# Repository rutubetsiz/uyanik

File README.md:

# UYANIK

[Türkçe](README.tr.md)

A device for turning a remote computer on and off. As long as you have internet access, it doesn’t matter where in the world you are.
## Why did I build this?

It started as a summer project. I had turned a spare computer into a server, but I didn’t want to leave it running all the time. University was about to start, and I needed a way to turn it on and off remotely. Shutting down a remote machine is easy, turning it on is not. Wake-on-LAN isn’t enough, and if you’re behind CGNAT on top of that... The answer to all of it was a device that stays on at home, so I built one. Wherever I am, UYANIK lets me open a web panel and turn my server on and off as if I were at home pressing the button on the case.

## How it works

The device connects to the motherboard’s front panel header (JFP1). When a command comes in, the optocoupler switches and the motherboard sees it as a button press. By reading the power LED line on the same header, it also knows whether the computer is on or off.

Since the device takes up the header, the case’s front panel is left out; there’s nowhere to plug in the case’s power button, reset button and LED. That’s why the device has its own power and reset buttons, plus an LED that shows whether the computer is on. So you don’t lose the case button, it just moves onto the device.

Commands go through Firebase Realtime Database. When you send a command from the panel, it’s written to a field in the database; the device polls that field and runs the command when it sees it. Status comes back the same way in the other direction.

The reason for Firebase is that the device and the phone are on different networks, usually behind CGNAT. A direct connection isn’t possible, so a meeting point is needed. No port forwarding, DDNS or static IP required.

Besides the remote panel there’s also a local panel. It lives in the device’s own flash and works without internet. If you’re on the same network, you can connect to the device directly and send commands. When the device can’t connect to any network, it opens its own hotspot and the same panel shows up as the setup screen.

The device has to keep running while the computer is off, after all it’s the thing that turns the machine on. I power it from the motherboard’s USB header, JUSB2. While the computer is off, the power on that header actually comes from the power supply’s standby line, which stays live as long as the plug is in. The motherboard doesn’t feed it to the header by default, so two BIOS settings need to be changed. Details are below under Power.

## Hardware

### Pins

GPIO25 drives the power button’s optocoupler, GPIO26 the reset button’s. GPIO27 reads the signal coming from the power LED’s optocoupler.

GPIO4 is reserved for factory reset. There’s no button for it on the board; to reset, short this pin to GND and hold it for five seconds without interruption.

GPIO32 was added in version 2. It drives an LED output that shows the computer is on.

### Parts

- ESP32-WROOM-32D
- 3x PC817 DIP-4 optocoupler
- 3x 470 ohm resistor
- 2x 3.5x6mm tact switch
- LED
- 3-pin slide on/off switch

To connect to JFP1, female front panel cables are enough if you can find them. Otherwise you can modify female-to-female jumper wires.

### Why an optocoupler?

I tried, as much as I could, to make this work on motherboards from different manufacturers, not just one. An optocoupler wasn’t strictly necessary; the buttons could have been driven with transistors and the power LED read directly through resistors. I chose the optocoupler because it doesn’t require making assumptions about the motherboard’s internal circuitry. The buttons’ pull-up voltage or which side the LED is driven from can vary from board to board, while an optocoupler works the same way on all of them. Since the cost difference is tiny, I went with the solution that isn’t affected by differences between boards.

### Power

The device needs to stay up while the computer is off. There are a few ways to do this.

One is from the motherboard, through the JUSB headers. This is how I did it. But there’s a catch: with default settings, the motherboard doesn’t supply standby power to the USB headers while it’s off. You need to change BIOS settings. The first is EuP 2013 or ErP Ready (the name depends on your board); on MSI it’s under Advanced, in the Power Management Setup menu. Set it to Disabled. The second is Resume By USB Device, also under Advanced but in the Wake Up Event Setup menu. Set it to Enabled. Measure between the header’s VCC and GND pins, you should see around 5 V. If you don’t, try the other header; some motherboards only supply standby power to certain ports. The downside: when the power goes out or the motherboard loses power, the device can’t get power until the computer is started by hand.

Another is directly from the power supply, pin 9 of the 24-pin connector. The purple wire. It’s completely independent of the BIOS because you’re taking power before the motherboard distributes it; no setting can turn it off. In return, you need a breakout board or a tap connector in between. If you don’t want to mess with the BIOS, or your motherboard never gives standby power to the headers, this way will definitely work.

A third option is to power the device directly from a battery or an adapter. The current design isn’t set up for that, so it would need modification.

### PCB

hardware/ contains the KiCad project and PDF exports.

I made the PCB myself, so I designed it to suit home etching. You can make it yourself, or open the KiCad project, change it to your liking and send it off to be manufactured. None of this is required, the circuit works on a breadboard too.

### Case

case/ contains the model.

You can 3D print it. All the parts are in one file, so you may need to separate them.

## Setup

### 1. Firmware

It builds with the Arduino IDE. The folder name has to match the .ino file, so open the software/UYANIK/ folder as it is.

If you edit panel.html, you need to regenerate the copy that gets embedded in the device:

```bash
python build_html.py
```

To check whether the two match:

```bash
python build_html.py --kontrol
```

### 2. First boot

On first boot the device prints three values to the serial port: the hotspot network name, the panel password and the OTA password.

```
SSID : UYANIK-XXXX
Password : ...
OTA : ...
```

Save these somewhere. They don’t change on factory reset. If you change the panel password later, the value here stops working, but a factory reset brings it back.

### 3. Wi-Fi

If no network is saved, the device opens its own hotspot. Once your phone is connected, go to uyanik.local to open the panel; if that doesn’t work, use 192.168.4.1.

After it joins a network, you can reach the device at uyanik.local or at the local IP shown in the panel. The hotspot stays up for another 25 seconds so you can see the new address.

### 4. Firebase

Everyone sets up their own Firebase project.

Create a new project in the Firebase console and add a Realtime Database to it. In the Authentication section, enable the Email/Password provider and create an account for the device.

Finally, lock the database rules to that account’s UID:

```json
{
  "rules": {
      ".read":  "auth != null && auth.uid === 'UID'",
      ".write": "auth != null && auth.uid === 'UID'"
  }
}
```

Once that’s done, enter the following in the Settings tab of the device’s panel: the Realtime Database URL, the Web API Key, the email and password of the account you created, and a device name.

### 5. Remote panel

software/web/public/index.html is a single static page and can be used in two ways.

To deploy it to Firebase Hosting, from the software/web/ folder:

```bash
firebase use --add
```

```bash
firebase deploy --only hosting
```

Since it’s a static file, you can also host it on your own server.

You can also open it directly via file://.

When the panel first opens, it asks for the database URL, the Web API Key and the device name. These are only stored in the browser and are never sent anywhere.

## Factory reset

Short GPIO 4 to GND and hold it for five seconds without interruption. A single break resets the counter.

A reset erases the Wi-Fi network and its password, the Firebase settings, the device and hotspot names, and the panel password if you changed it. It does not touch the panel and OTA passwords generated on first boot.

## Read more

- [Troubleshooting](docs/TROUBLESHOOTING.md)
- [Firmware structure](docs/FIRMWARE.md)

## License

GPL-3.0. See [LICENSE](LICENSE) for details.

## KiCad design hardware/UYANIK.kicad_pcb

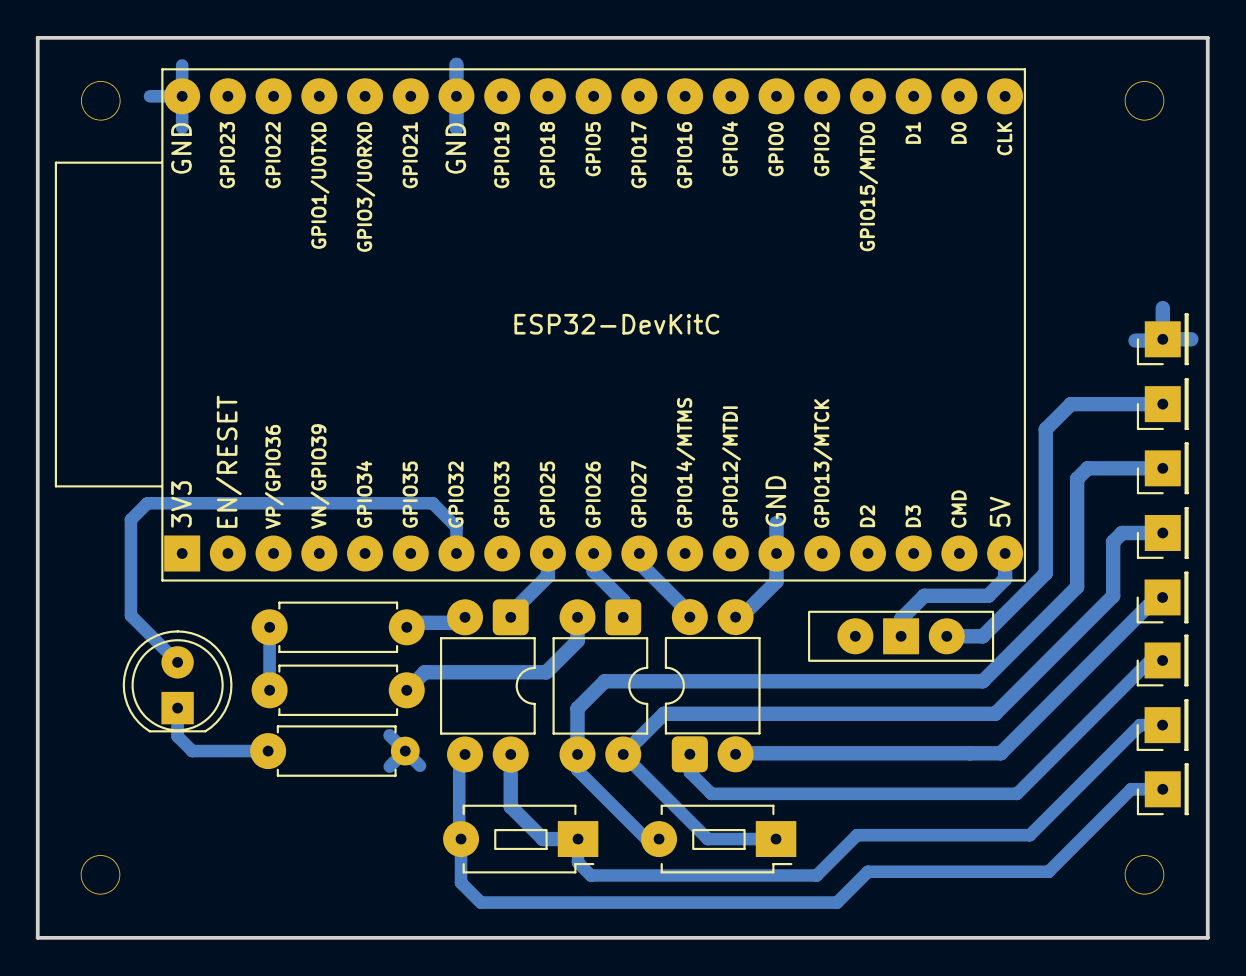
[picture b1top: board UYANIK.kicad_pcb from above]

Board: 2 copper layers, 65.0 x 50.0 mm, 19 parts (0 on the bottom side), 16 nets.

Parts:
D1: POWER LED; LED_D5.0mm
J1: POWER SW+; PinHeader_1x01_P2.54mm_Vertical
J2: POWER SW-; PinHeader_1x01_P2.54mm_Vertical
J3: RESET SW+; PinHeader_1x01_P2.54mm_Vertical
J4: RESET SW-; PinHeader_1x01_P2.54mm_Vertical
J5: POWER LED+; PinHeader_1x01_P2.54mm_Vertical
J6: POWER LED-; PinHeader_1x01_P2.54mm_Vertical
J13: VSS; PinHeader_1x01_P2.54mm_Vertical
J14: VCC; PinHeader_1x01_P2.54mm_Vertical
R1, R2, R3: 470; R_Axial_DIN0207_L6.3mm_D2.5mm_P7.62mm_Horizontal
SW1: SW_RESET; SW_PUSH_1P1T_6x3.5mm_H4.3_APEM_MJTP1243
SW2: SW_POWER; SW_PUSH_1P1T_6x3.5mm_H4.3_APEM_MJTP1243
SW3: ON / OFF; SW_Slide-03_Wuerth-WS-SLTV_10x2.5x6.4_P2.54mm
U2: RST OPT; DIP-4_W7.62mm
U3: ESP32-DevKitC
U4: PWR OPT; DIP-4_W7.62mm
U5: LED OPT; DIP-4_W7.62mm

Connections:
GND: J13.1 (Pin_1_1), R1.2, R2.2, R3.2, U3.14 (GND), U3.32 (GND), U3.38 (GND), U5.3
GPIO25: U3.9 (DAC_1/ADC2_CH8/GPIO25), U4.1
GPIO26: U2.1, U3.10 (DAC_2/ADC2_CH9/GPIO26)
GPIO27: U3.11 (ADC2_CH7/GPIO27), U5.4
unnamed: D1.2 (A), U3.7 (32K_XP/GPIO32/ADC1_CH4)
unnamed: D1.1 (K), R3.1
unnamed: J1.1 (Pin_1_1), SW2.1, U4.4
unnamed: J2.1 (Pin_1_1), SW2.2, U4.3
unnamed: J3.1 (Pin_1_1), SW1.1, U2.4
unnamed: J4.1 (Pin_1_1), SW1.2, U2.3
unnamed: J5.1 (Pin_1_1), U5.1
unnamed: J6.1 (Pin_1_1), U5.2
unnamed: J14.1 (Pin_1_1), SW3.2 (B)
unnamed: R1.1, U4.2
unnamed: R2.1, U2.2
unnamed: SW3.1 (A), U3.19 (5V)
